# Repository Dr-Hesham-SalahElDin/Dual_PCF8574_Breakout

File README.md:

# PCF8574 Dual I/O Expander Breakout Board

## Overview
This project is a **breakout board for two PCF8574 I/O expanders**, providing **16 digital I/O pins** (8 per expander) via **I²C communication**.  
The board allows users to configure the I²C addresses using **0Ω resistors**, making it flexible for different applications.

## Features
- **Dual PCF8574 ICs** providing **16 GPIOs**
- **I²C interface** for simple microcontroller integration
- **Configurable I²C addresses** using **0Ω resistors**
- **Onboard pull-up resistors** for I²C stability

## I²C Address Configuration
Each **PCF8574** has a **7-bit address**, where the lower 3 bits (`A2, A1, A0`) are user-configurable using **0Ω resistors**.

- **To set a bit to `0` (GND):** Solder the **0Ω resistor** between the address pin and **GND**.
- **To set a bit to `1` (VCC):** Solder the **0Ω resistor** between the address pin and **VCC**.

### Example Address Configurations
| A2 | A1 | A0 | I²C Address |
|----|----|----|------------|
| 0  | 0  | 0  | `0x20` |
| 0  | 0  | 1  | `0x21` |
| 0  | 1  | 0  | `0x22` |
| 0  | 1  | 1  | `0x23` |
| 1  | 0  | 0  | `0x24` |
| 1  | 0  | 1  | `0x25` |
| 1  | 1  | 0  | `0x26` |
| 1  | 1  | 1  | `0x27` |

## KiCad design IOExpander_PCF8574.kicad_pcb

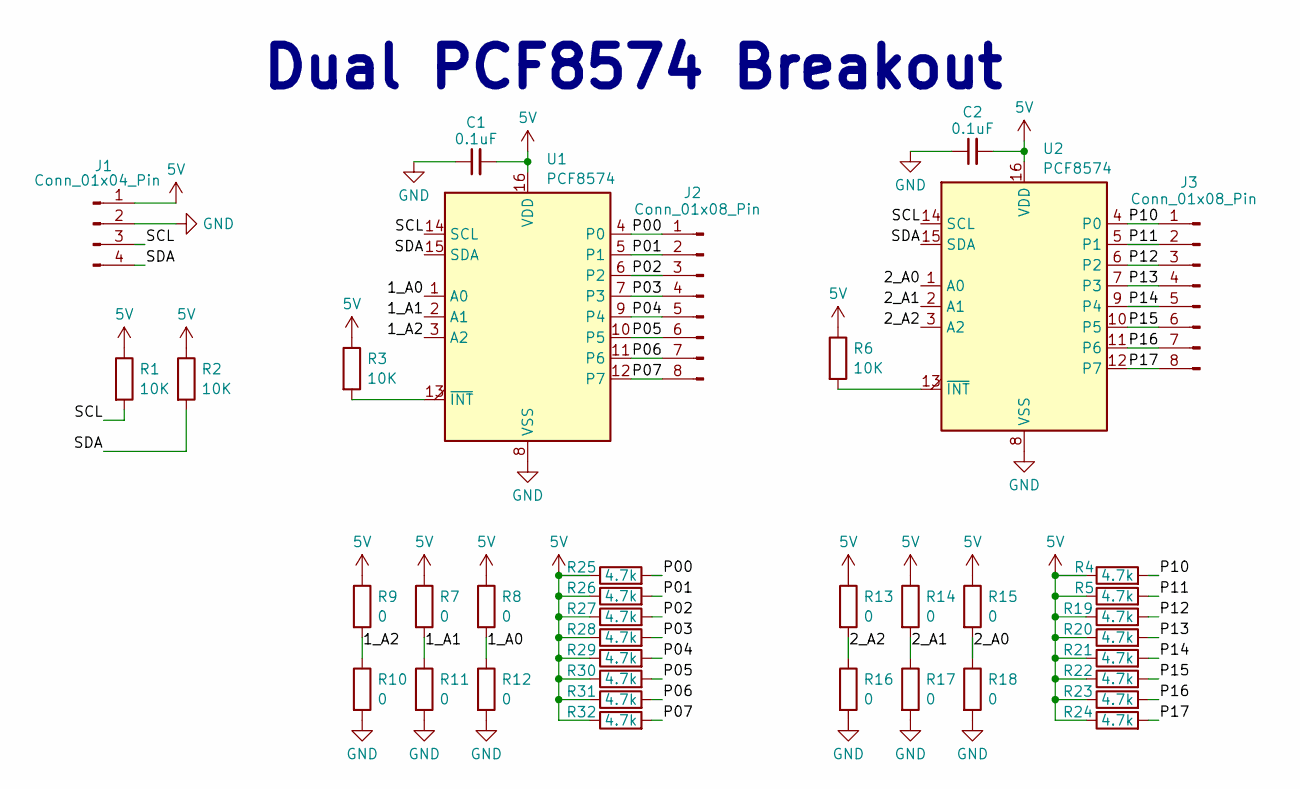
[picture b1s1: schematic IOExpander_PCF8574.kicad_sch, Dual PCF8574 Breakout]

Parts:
C1, C2: 0.1uF; C_1206_3216Metric_Pad1.33x1.80mm_HandSolder
J1: Conn_01x04_Pin; JST_XH_S4B-XH-A-1_1x04_P2.50mm_Horizontal
J2, J3: Conn_01x08_Pin; PinHeader_1x08_P2.54mm_Vertical
R1, R2, R3, R6: 10K; R_1206_3216Metric_Pad1.30x1.75mm_HandSolder
R4, R5, R19, R20, R21, R22, R23, R24, R25, R26, R27, R28, R29, R30, R31, R32: 4.7k; R_1206_3216Metric_Pad1.30x1.75mm_HandSolder
R7, R8, R9, R10, R11, R12, R13, R14, R15, R16, R17, R18: 0; R_1206_3216Metric_Pad1.30x1.75mm_HandSolder
U1, U2: PCF8574; SO-16_5.3x10.2mm_P1.27mm

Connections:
5V: C1.2, C2.2, J1.1, R1.1, R2.1, R3.1, R4.1, R5.1, R6.1, R7.1, R8.1, R9.1, R13.1, R14.1, R15.1, R19.1, R20.1, R21.1, R22.1, R23.1, R24.1, R25.1, R26.1, R27.1, R28.1, R29.1, R30.1, R31.1, R32.1, U1.16 (VDD), U2.16 (VDD)
/1_A0: R8.2, R12.1, U1.1 (A0)
/1_A1: R7.2, R11.1, U1.2 (A1)
/1_A2: R9.2, R10.1, U1.3 (A2)
/2_A0: R15.2, R18.1, U2.1 (A0)
/2_A1: R14.2, R17.1, U2.2 (A1)
/2_A2: R13.2, R16.1, U2.3 (A2)
/P00: J2.1, R25.2, U1.4 (P0)
/P01: J2.2, R26.2, U1.5 (P1)
/P02: J2.3, R27.2, U1.6 (P2)
/P03: J2.4, R28.2, U1.7 (P3)
/P04: J2.5, R29.2, U1.9 (P4)
/P05: J2.6, R30.2, U1.10 (P5)
/P06: J2.7, R31.2, U1.11 (P6)
/P07: J2.8, R32.2, U1.12 (P7)
/P10: J3.1, R4.2, U2.4 (P0)
/P11: J3.2, R5.2, U2.5 (P1)
/P12: J3.3, R19.2, U2.6 (P2)
/P13: J3.4, R20.2, U2.7 (P3)
/P14: J3.5, R21.2, U2.9 (P4)
/P15: J3.6, R22.2, U2.10 (P5)
/P16: J3.7, R23.2, U2.11 (P6)
/P17: J3.8, R24.2, U2.12 (P7)
/SCL: J1.3, R1.2, U1.14 (SCL), U2.14 (SCL)
/SDA: J1.4, R2.2, U1.15 (SDA), U2.15 (SDA)
GND: C1.1, C2.1, J1.2, R10.2, R11.2, R12.2, R16.2, R17.2, R18.2, U1.8 (VSS), U2.8 (VSS)
unnamed: R3.2, U1.13 (~INT)
unnamed: R6.2, U2.13 (~INT)

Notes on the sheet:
Dual PCF8574 Breakout

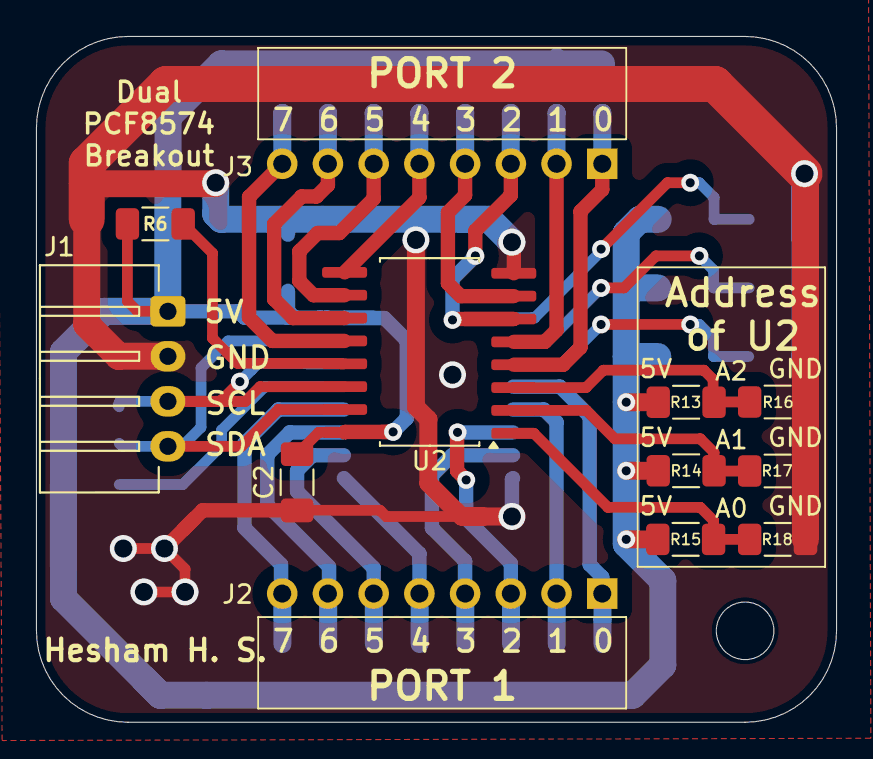
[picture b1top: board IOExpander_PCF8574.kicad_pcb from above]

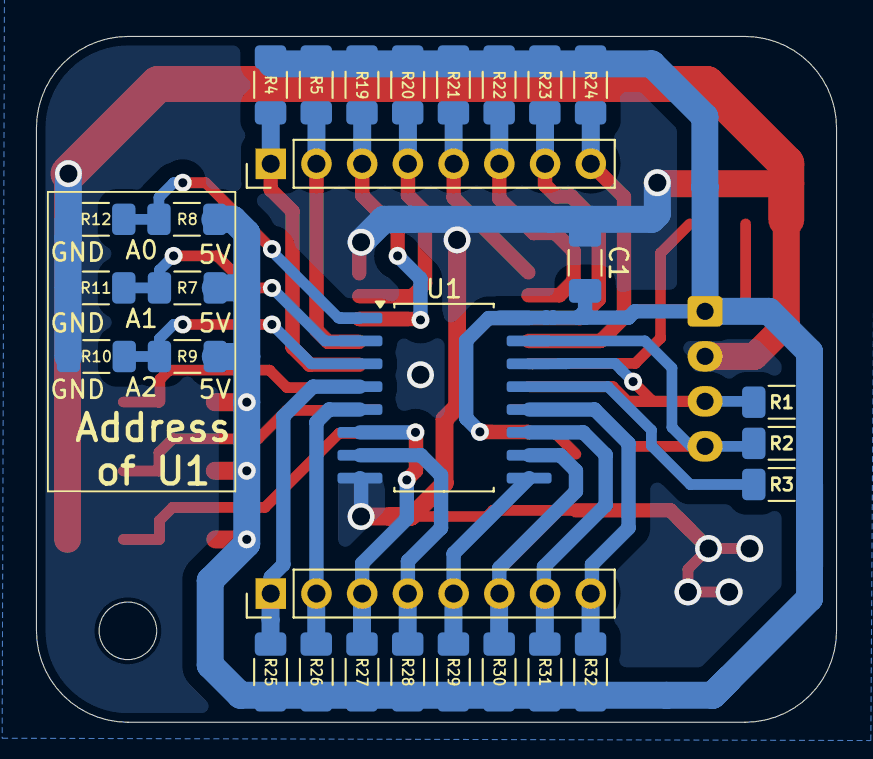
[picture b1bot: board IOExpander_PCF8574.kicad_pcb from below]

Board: 2 copper layers, 44.5 x 38.1 mm, 39 parts (29 on the bottom side), 28 nets.

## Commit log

2025-02-03 Updated the PCB Layout Silkscreen layer
2025-02-03 Updated the Drawing SheetModified
2025-02-04 Coupling Capacitors added
2025-02-04 Modyfied Readme File
2025-02-12 editing the footprint of PCF8574
2025-02-12 updating the screenshots
2025-04-15 Pull Up resistors are added for each channel
